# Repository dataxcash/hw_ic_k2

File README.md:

# hw_ic_k2 — K2 PCIe Gen4 Converter Card (x8 → 2× x4)

**English** | [简体中文](README.zh-CN.md)

Open-source hardware — KiCad design files for the **K2 converter card**, the
worker-side data-plane card in the IOCONVERT V2.0 1-Master-to-4-Worker chained
NTB cluster. It takes one x8 host link and fans it out to two x4 MCIO ports,
redriven for PCIe Gen4 signal integrity.

## Preview

**Current fabrication release (`m7t8a`)** — annotated 3D render (connector entry
directions, pin-1 markers and part labels verified against the board):

Board file: `pm_gate/artifacts/k2_v4/L6/board/k2_v4_8L.m7t8a.kicad_pcb`

*3D renders use KiCad stock models for standard packages. The MCIO (SFF-1016) and
SlimSAS (SFF-8654) connectors have no vendor 3D models and are represented by
simplified models derived from their footprint geometry (entry direction and
pin-1 markers placed per footprint placement).*

## Overview

K2 sits between the master host and the worker devices. A single SlimSAS x8
uplink carries eight PCIe Gen4 lanes; the card redrives them (per-lane AC
coupling is integrated in the device), then splits them across two MCIO 4i
downlinks (4 lanes each). A single DS320PR1601 redriver (U6) handles the link,
and an on-board STM32G0B1 MCU manages sideband, out-of-band UART, I2C and the
FRU EEPROM.

```
                8 lanes                       2 × 4 lanes
  Master ─────────────────►  K2  ──────────────────────────► MCIO 4i (J3) → worker
  (SlimSAS x8,              │    AC coupling + redrive
   SFF-8654, J2)            └──────────────────────────────► MCIO 4i (J4) → worker

                            U6 = DS320PR1601 redriver
                            STM32G0B1 MCU · 12V DC-in
```

## Key Features

- **Form factor**: 8-layer PCB, 120 × 46 mm, 85Ω ±10% differential impedance
- **Uplink**: 1× SlimSAS x8 (SFF-8654) — 8 PCIe Gen4 lanes + 2 reference clocks
- **Downlink**: 2× MCIO 4i (SFF-1016) — the x8 link is bifurcated into 2× x4
- **Redrivers**: single DS320PR1601 (U6); per-lane AC coupling is integrated in the device
- **Management**: STM32G0B1 MCU — sideband, OOB UART, I2C, FRU EEPROM
- **Power**: 12V DC-in → DC-DC 5V → LDO 3V3, plus 3.3V_AUX
- **Debug**: SWD header (J13), OOB UART header (J9)

## Repository Contents

| Path | Description |
|---|---|
| `hw/` | KiCad project (current 8L revision) |
| `hw/sch/` | Schematics: connectors, AC-coupling & ReDriver strap (up/down), MCU & sideband, power |
| `hw/lib/` | Symbol + footprint libraries |
| `hw/data/` | Netlist / project configuration (YAML) |
| `archive/k2_v4_6L/` | Historical 6L revision (superseded by 8L) |
| `docs/` | Architecture and manufacturing notes |

## Getting Started

1. Install [KiCad](https://www.kicad.org/) 10.x
2. Clone this repository
3. Open `hw/k2_v4_8L.kicad_pro`
4. If symbols/footprints show as missing, add `hw/lib/DS320PR1601.kicad_sym` to
   the symbol library table and `hw/lib/ForgeOS.pretty/` to the footprint
   library table (global or project-level)

## Key Files

| File | Meaning |
|---|---|
| `hw/k2_v4_8L.kicad_pcb` | **Design source** (frozen input) |
| `pm_gate/artifacts/k2_v4/L6/board/k2_v4_8L.m7t8a.kicad_pcb` | **Fabrication release board** (ready to order) |

## Documentation

- [`docs/01-architecture.md`](docs/01-architecture.md) — What this card is
- [`docs/02-manufacturing.md`](docs/02-manufacturing.md) — Stackup / process / delivery

## License

AGPL-3.0 (see `LICENSE`)

---

*Part of the IOCONVERT V2.0 family: [hw_ic_k1](https://github.com/dataxcash/hw_ic_k1) (master gate card) · [hw_ic_key](https://github.com/dataxcash/hw_ic_key) (secure key vault)*

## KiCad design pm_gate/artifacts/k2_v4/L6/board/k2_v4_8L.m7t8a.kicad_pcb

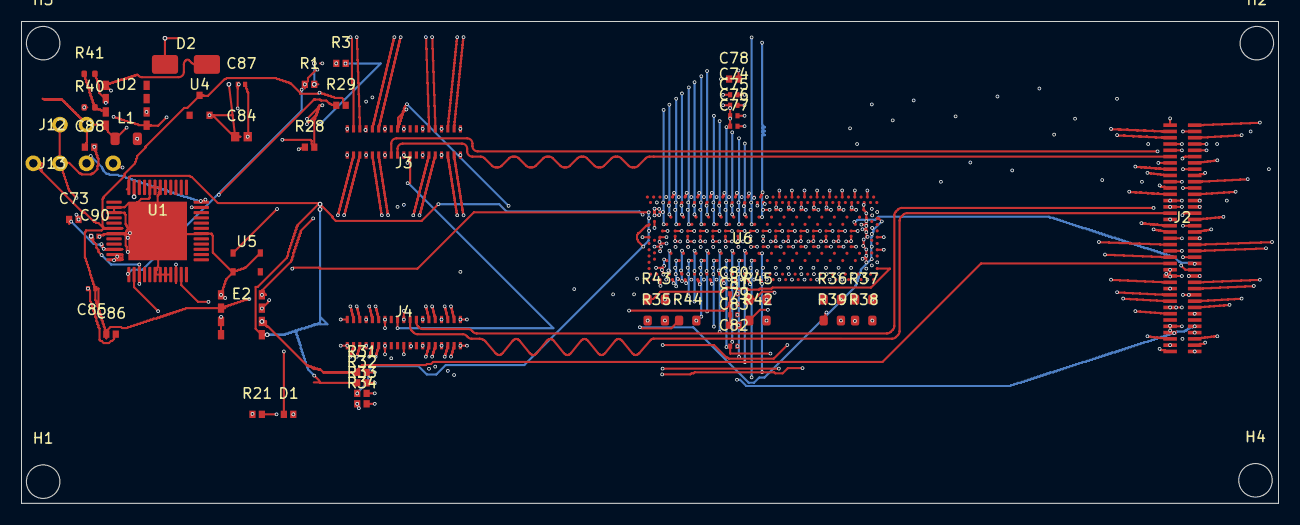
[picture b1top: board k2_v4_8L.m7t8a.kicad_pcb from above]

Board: 8 copper layers, 120.0 x 46.0 mm, 55 parts (0 on the bottom side), 97 nets.

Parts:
C73: 100nF; C_0402_1005Metric__3
C74, C75, C76, C77, C79, C80, C81, C82, C87, C90: 100nF; C_0402_1005Metric__1
C78, C83, C88: 1uF; C_0603_1608Metric
C84: 10uF; C_0805_2012Metric
C85: 100nF; C_0402_1005Metric__2
C86: 4.7uF; C_0603_1608Metric
D1: LED; LED_0603_1608Metric
D2: SS34; D_SMA
E2: FRU_EEPROM; SOIC8_FRU
H1, H2, H3, H4: MountingHole_3.2mm_M3
J2: SlimSAS_x8_SFF8654; SlimSAS_x8_SFF-8654_74pin_RASide
J3: MCIO_4i_SFF1016; MCIO_4i_SFF-1016_RASide__1
J4: MCIO_4i_SFF1016; MCIO_4i_SFF-1016_RASide__2
J12: J_12V_IN; PinHeader_1x02
J13: J_SWD; PinHeader_1x04
L1: 10µH; L_0805_2012Metric
R1, R28, R29: 10K; R_0603_1608Metric__1
R3: 220R; R_0603_1608Metric__1
R21: 1K; R_0603_1608Metric__1
R31, R32, R33, R34: 4.7k; R_0603_1608Metric__1
R35: R_6K19; R_0603_1608Metric__2
R36, R37, R39, R42, R43, R44, R45: 1K; R_0603_1608Metric__2
R38: R_8K25; R_0603_1608Metric__2
R40: 10K; R_0402_1005Metric__2
R41: 5.6k; R_0402_1005Metric__1
U1: STM32G0B1CBT6; MCU_STM32G0_LQFP48
U2: DCDC_12V_3V3; SOIC-8_5.3x5.3mm_P1.27mm
U4: BAT54C; SOT23_BAT54C
U5: OPTO_LTV356T
U6: DS320PR1601

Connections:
12V_IN: C88.1, J12.1, L1.1, U2.4, U2.6
DS320_STRAP_A_ADDR0_7-0: R36.1, U6.B23
DS320_STRAP_A_ADDR0_15-8: R42.1, U6.FF5
DS320_STRAP_A_ADDR1_7-0: R37.1, U6.G1
DS320_STRAP_A_ADDR1_15-8: R43.1, U6.FJ3
DS320_STRAP_B_ADDR0_7-0: R38.1, U6.B25
DS320_STRAP_B_ADDR0_15-8: R44.1, U6.FJ28
DS320_STRAP_B_ADDR1_7-0: R39.1, U6.F34
DS320_STRAP_B_ADDR1_15-8: R45.1, U6.FF30
DS320_STRAP_MODE: R35.1, U6.FF24
FB_U2: R40.2, R41.1, U2.3
GND: C73.2, C74.2, C75.2, C76.2, C77.2, C78.2, C79.2, C80.2, C81.2, C82.2, C83.2, C84.2, C85.2, C86.2, C87.2, C88.2, C90.2, D1.1, E2.1, E2.3, E2.4, E2.7, J2.1, J2.4, J2.7, J2.8, J2.9, J2.10, J2.13, J2.16, J2.19, J2.22, J2.25, J2.26, J2.27, J2.28, J2.31, J2.34, J2.37, J2.38, J2.41, J2.44, J2.47, J2.49, J2.50, J2.53, J2.56, J2.59, J2.62, J2.65, J2.67, J2.68, J2.71, J2.74, J3.A1, J3.A4, J3.A7, J3.A10, J3.A13, J3.A16, J3.A19, J3.B1, J3.B4, J3.B7, J3.B10, J3.B13, J3.B16, J3.B19, J4.A1, J4.A4, J4.A7, J4.A10, J4.A13, J4.A16, J4.A19, J4.B1, J4.B4, J4.B7, J4.B10, J4.B13, J4.B16, J4.B19, J12.2, J13.3, R28.2, R35.2, R36.2, R37.2, R38.2, R39.2, R41.2, R42.2, R43.2, R44.2, R45.2, U1.2, U1.3, U1.7, U1.18, U1.19, U1.20, U1.21, U1.30, U1.42, U1.43, U1.44, U1.49, U2.2, U5.2, U5.3, U6.AC4, U6.AC13, U6.AC22, U6.AC32, U6.AD2, U6.AD34, U6.AE1, U6.AE35, U6.AK4, U6.AK13, U6.AK22, U6.AK32, U6.AL2, U6.AL34, U6.AM1, U6.AM35, U6.AU4, U6.AU13, U6.AU22, U6.AU32, U6.AV2, U6.AV34, U6.AW1, U6.AW35, U6.B19, U6.BD4, U6.BD13, U6.BD22, U6.BD32, U6.BE2, U6.BE34, U6.BF1, U6.BF35, U6.BL4, U6.BL13, U6.BL22, U6.BL32, U6.BM2, U6.BM34, U6.BN1, U6.BN35, U6.BV4, U6.BV13, U6.BV22, U6.BV32, U6.BW2, U6.BW34, U6.BY1, U6.BY35, U6.CE4, U6.CE13, U6.CE22, U6.CE32, U6.CF2, U6.CF34, U6.CG1, U6.CG35, U6.CM4, U6.CM13, U6.CM22, U6.CM32, U6.CN2, U6.CN34, U6.CP1, U6.CP35, U6.CW4, U6.CW13, U6.CW22, U6.CW32, U6.CY2, U6.CY34, U6.DA1, U6.DA35, U6.DF4, U6.DF13, U6.DF22, U6.DF32, U6.DG2, U6.DG34, U6.DH1, U6.DH35, U6.DN4, U6.DN13, U6.DN22, U6.DN32, U6.DP2, U6.DP34, U6.DR1, U6.DR35, U6.DY4, U6.DY13, U6.DY22, U6.DY32, U6.E14, U6.E27, U6.E30, U6.E33, U6.EA2, U6.EA34, U6.EB1, U6.EB35, U6.EG4, U6.EG13, U6.EG22, U6.EG32, U6.EH2, U6.EH34, U6.EJ1, U6.EJ35, U6.EP4, U6.EP13, U6.EP22, U6.EP32, U6.ER2, U6.ER34, U6.ET1, U6.ET35, U6.FA15, U6.FA32, U6.FB2, U6.FB34, U6.FC3, U6.FC6, U6.FC9, U6.FC19, U6.FC23, U6.FC25, U6.FC28, U6.FD1, U6.FD35, U6.FF14, U6.FF21, U6.FF33, U6.FJ12, U6.FJ19, U6.FJ31, U6.H12, U6.H16, U6.H19, U6.H31, U6.J4, U6.J22, U6.K2, U6.K34, U6.L1, U6.L35, U6.T4, U6.T13, U6.T22, U6.T32, U6.U2, U6.U34, U6.V1, U6.V35
GPIO_LED: R21.1, U1.14
I2C1_SCL: E2.6, J2.45, R31.1, U1.47
I2C1_SDA: E2.5, J2.46, R32.1, U1.48
I2C2_SCL: R33.1, U1.22, U6.B31
I2C2_SDA: R34.1, U1.23, U6.B28
LED_A: D1.2, R21.2
MCU_VDD: C85.1, C86.1, E2.2, E2.8, J13.4, R29.2, R31.2, R32.2, R33.2, R34.2, U1.6, U4.3
NRST: C73.1, R29.1, U1.10
P3V3: C74.1, C75.1, C76.1, C77.1, C78.1, C79.1, C80.1, C81.1, C82.1, C83.1, C84.1, D2.1, R40.1, U2.5, U4.2, U6.AC17, U6.AC20, U6.AK17, U6.AK20, U6.AU17, U6.AU20, U6.BD17, U6.BD20, U6.BL17, U6.BL20, U6.BV17, U6.BV20, U6.CE17, U6.CE20, U6.CM17, U6.CM20, U6.CW17, U6.CW20, U6.DF17, U6.DF20, U6.DN17, U6.DN20, U6.DY17, U6.DY20, U6.EG17, U6.EG20, U6.EP17, U6.EP20, U6.FF8, U6.FJ6, U6.T17, U6.T20
P3V3_AUX: C90.1, J3.A9, J4.A9, R1.2, U1.15
PCIE_DN0_N: J2.40, U6.R1
PCIE_DN0_P: J2.39, U6.N2
PCIE_DN1_N: J2.43, U6.AB1
PCIE_DN1_P: J2.42, U6.Y2
PCIE_DN2_N: J2.52, U6.AG2
PCIE_DN2_P: J2.51, U6.AJ1
PCIE_DN3_N: J2.55, U6.AP2
PCIE_DN3_P: J2.54, U6.AT1
PCIE_DN4_N: J2.58, U6.BC1
PCIE_DN4_P: J2.57, U6.BA2
PCIE_DN5_N: J2.61, U6.BK1
PCIE_DN5_P: J2.60, U6.BH2
PCIE_DN6_N: J2.70, U6.BR2
PCIE_DN6_P: J2.69, U6.BU1
PCIE_DN7_N: J2.73, U6.CB2
PCIE_DN7_P: J2.72, U6.CD1
PCIE_DN_OUT0_N_MCIO: J3.A3, U6.P29
PCIE_DN_OUT0_P_MCIO: J3.A2, U6.M26
PCIE_DN_OUT1_N_MCIO: J3.A6, U6.AA29
PCIE_DN_OUT1_P_MCIO: J3.A5, U6.W26
PCIE_DN_OUT2_N_MCIO: J3.A15, U6.AH29
PCIE_DN_OUT2_P_MCIO: J3.A14, U6.AF26
PCIE_DN_OUT3_N_MCIO: J3.A18, U6.AR29
PCIE_DN_OUT3_P_MCIO: J3.A17, U6.AN26
PCIE_DN_OUT4_N_MCIO: J4.A3, U6.BB29
PCIE_DN_OUT4_P_MCIO: J4.A2, U6.AY26
PCIE_DN_OUT5_N_MCIO: J4.A6, U6.BJ29
PCIE_DN_OUT5_P_MCIO: J4.A5, U6.BG26
PCIE_DN_OUT6_N_MCIO: J4.A15, U6.BT29
PCIE_DN_OUT6_P_MCIO: J4.A14, U6.BP26
PCIE_DN_OUT7_N_MCIO: J4.A18, U6.CC29
PCIE_DN_OUT7_P_MCIO: J4.A17, U6.CA26
PCIE_REFCLK0_N: J2.12, J3.A12
PCIE_REFCLK0_P: J2.11, J3.A11
PCIE_REFCLK1_N: J2.30, J4.A12
PCIE_REFCLK1_P: J2.29, J4.A11
PCIE_UP0_N: J3.B3, U6.N34
PCIE_UP0_P: J3.B2, U6.R35
PCIE_UP1_N: J3.B6, U6.Y34
PCIE_UP1_P: J3.B5, U6.AB35
PCIE_UP2_N: J3.B15, U6.AJ35
PCIE_UP2_P: J3.B14, U6.AG34
PCIE_UP3_N: J3.B18, U6.AT35
PCIE_UP3_P: J3.B17, U6.AP34
PCIE_UP4_N: J4.B3, U6.BA34
PCIE_UP4_P: J4.B2, U6.BC35
PCIE_UP5_N: J4.B6, U6.BH34
PCIE_UP5_P: J4.B5, U6.BK35
PCIE_UP6_N: J4.B15, U6.BU35
PCIE_UP6_P: J4.B14, U6.BR34
PCIE_UP7_N: J4.B18, U6.CD35
PCIE_UP7_P: J4.B17, U6.CB34
PCIE_UP_OUT0_N_J2: J2.3, U6.M7
PCIE_UP_OUT0_P_J2: J2.2, U6.P10
PCIE_UP_OUT1_N_J2: J2.6, U6.W7
PCIE_UP_OUT1_P_J2: J2.5, U6.AA10
PCIE_UP_OUT2_N_J2: J2.15, U6.AF7
PCIE_UP_OUT2_P_J2: J2.14, U6.AH10
PCIE_UP_OUT3_N_J2: J2.18, U6.AN7
PCIE_UP_OUT3_P_J2: J2.17, U6.AR10
PCIE_UP_OUT4_N_J2: J2.21, U6.AY7
PCIE_UP_OUT4_P_J2: J2.20, U6.BB10
PCIE_UP_OUT5_N_J2: J2.24, U6.BG7
PCIE_UP_OUT5_P_J2: J2.23, U6.BJ10
PCIE_UP_OUT6_N_J2: J2.33, U6.BP7
PCIE_UP_OUT6_P_J2: J2.32, U6.BT10
PCIE_UP_OUT7_N_J2: J2.36, U6.CA7
PCIE_UP_OUT7_P_J2: J2.35, U6.CC10
PERSTA#: C87.1, J2.48, J3.B11, R1.1, U1.11, U1.12
PERSTB#: J2.66, J4.B11
PWR_BTN_ISO: R3.2, U5.1
PWR_BTN_OUT: R3.1, U1.13
SWCLK_BOOT0: J13.2, R28.1, U1.36
SWDIO: J13.1, U1.35
SW_U2: D2.2, L1.2, U2.1
